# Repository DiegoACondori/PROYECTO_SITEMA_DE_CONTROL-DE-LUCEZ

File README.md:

# PROYECTO_SITEMA_DE_CONTROL_DE_LUCEZ

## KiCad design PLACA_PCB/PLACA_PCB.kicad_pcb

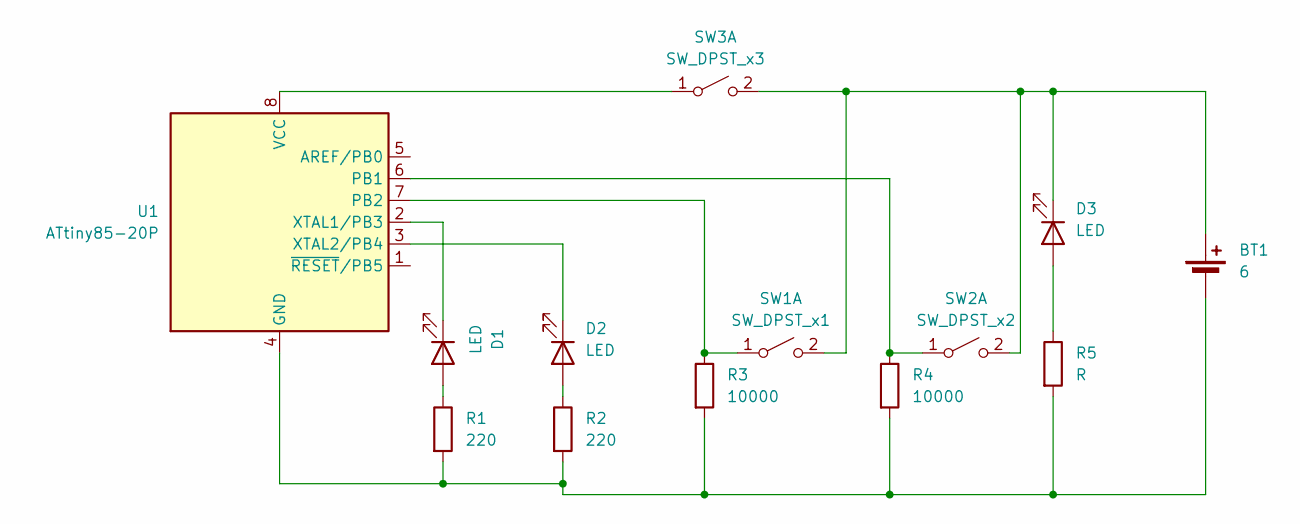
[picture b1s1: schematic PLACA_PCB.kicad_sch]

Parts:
BT1: 6; BatteryHolder_Keystone_1042_1x18650
D1, D2, D3: LED; LED_D3.0mm_Clear
R1, R2: 220; R_Axial_DIN0617_L17.0mm_D6.0mm_P30.48mm_Horizontal
R3, R4: 10000; R_Axial_DIN0617_L17.0mm_D6.0mm_P30.48mm_Horizontal
R5: R; R_Axial_DIN0617_L17.0mm_D6.0mm_P30.48mm_Horizontal
SW1: SW_DPST_x1; SW_SPST_REED_CT05-XXXX-G1
SW2: SW_DPST_x2; SW_SPST_REED_CT05-XXXX-G1
SW3: SW_DPST_x3; SW_SPST_REED_CT05-XXXX-G1
U1: ATtiny85-20P; DIP-8_W7.62mm

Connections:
unnamed: BT1.1 (+), D3.1 (K), SW1.2 (B), SW2.2 (B), SW3.2 (B)
unnamed: BT1.2 (-), R1.2, R2.2, R3.2, R4.2, R5.2, U1.4 (GND)
unnamed: D1.2 (A), R1.1
unnamed: D1.1 (K), U1.2 (XTAL1/PB3)
unnamed: D2.2 (A), R2.1
unnamed: D2.1 (K), U1.3 (XTAL2/PB4)
unnamed: D3.2 (A), R5.1
unnamed: R3.1, SW1.1 (A), U1.7 (PB2)
unnamed: R4.1, SW2.1 (A), U1.6 (PB1)
unnamed: SW3.1 (A), U1.8 (VCC)

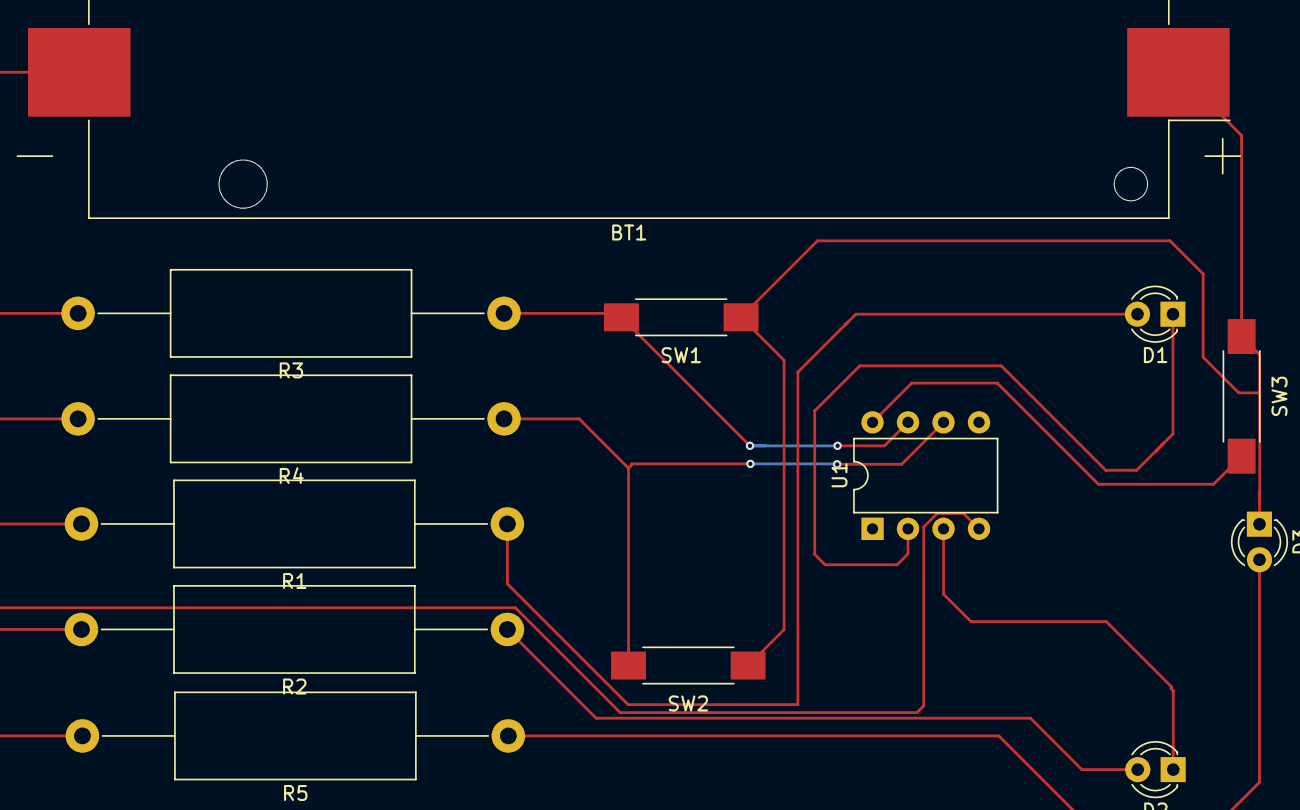
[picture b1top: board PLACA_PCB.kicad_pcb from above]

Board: 2 copper layers, 13 parts (0 on the bottom side), 10 nets.

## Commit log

2024-04-13 Actualizacion
2024-06-15 SISTEMA_DE_LUCEZ
2024-06-15 PLACA PCB
